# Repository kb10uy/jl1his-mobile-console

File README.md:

# JL1HIS Moblile Console

## License

firmware/app/assets/ 以下のテキスト群はそれぞれのファイルの出典に基づく。
それ以外は各ディレクトリの LICENSE ファイルに準ずる。

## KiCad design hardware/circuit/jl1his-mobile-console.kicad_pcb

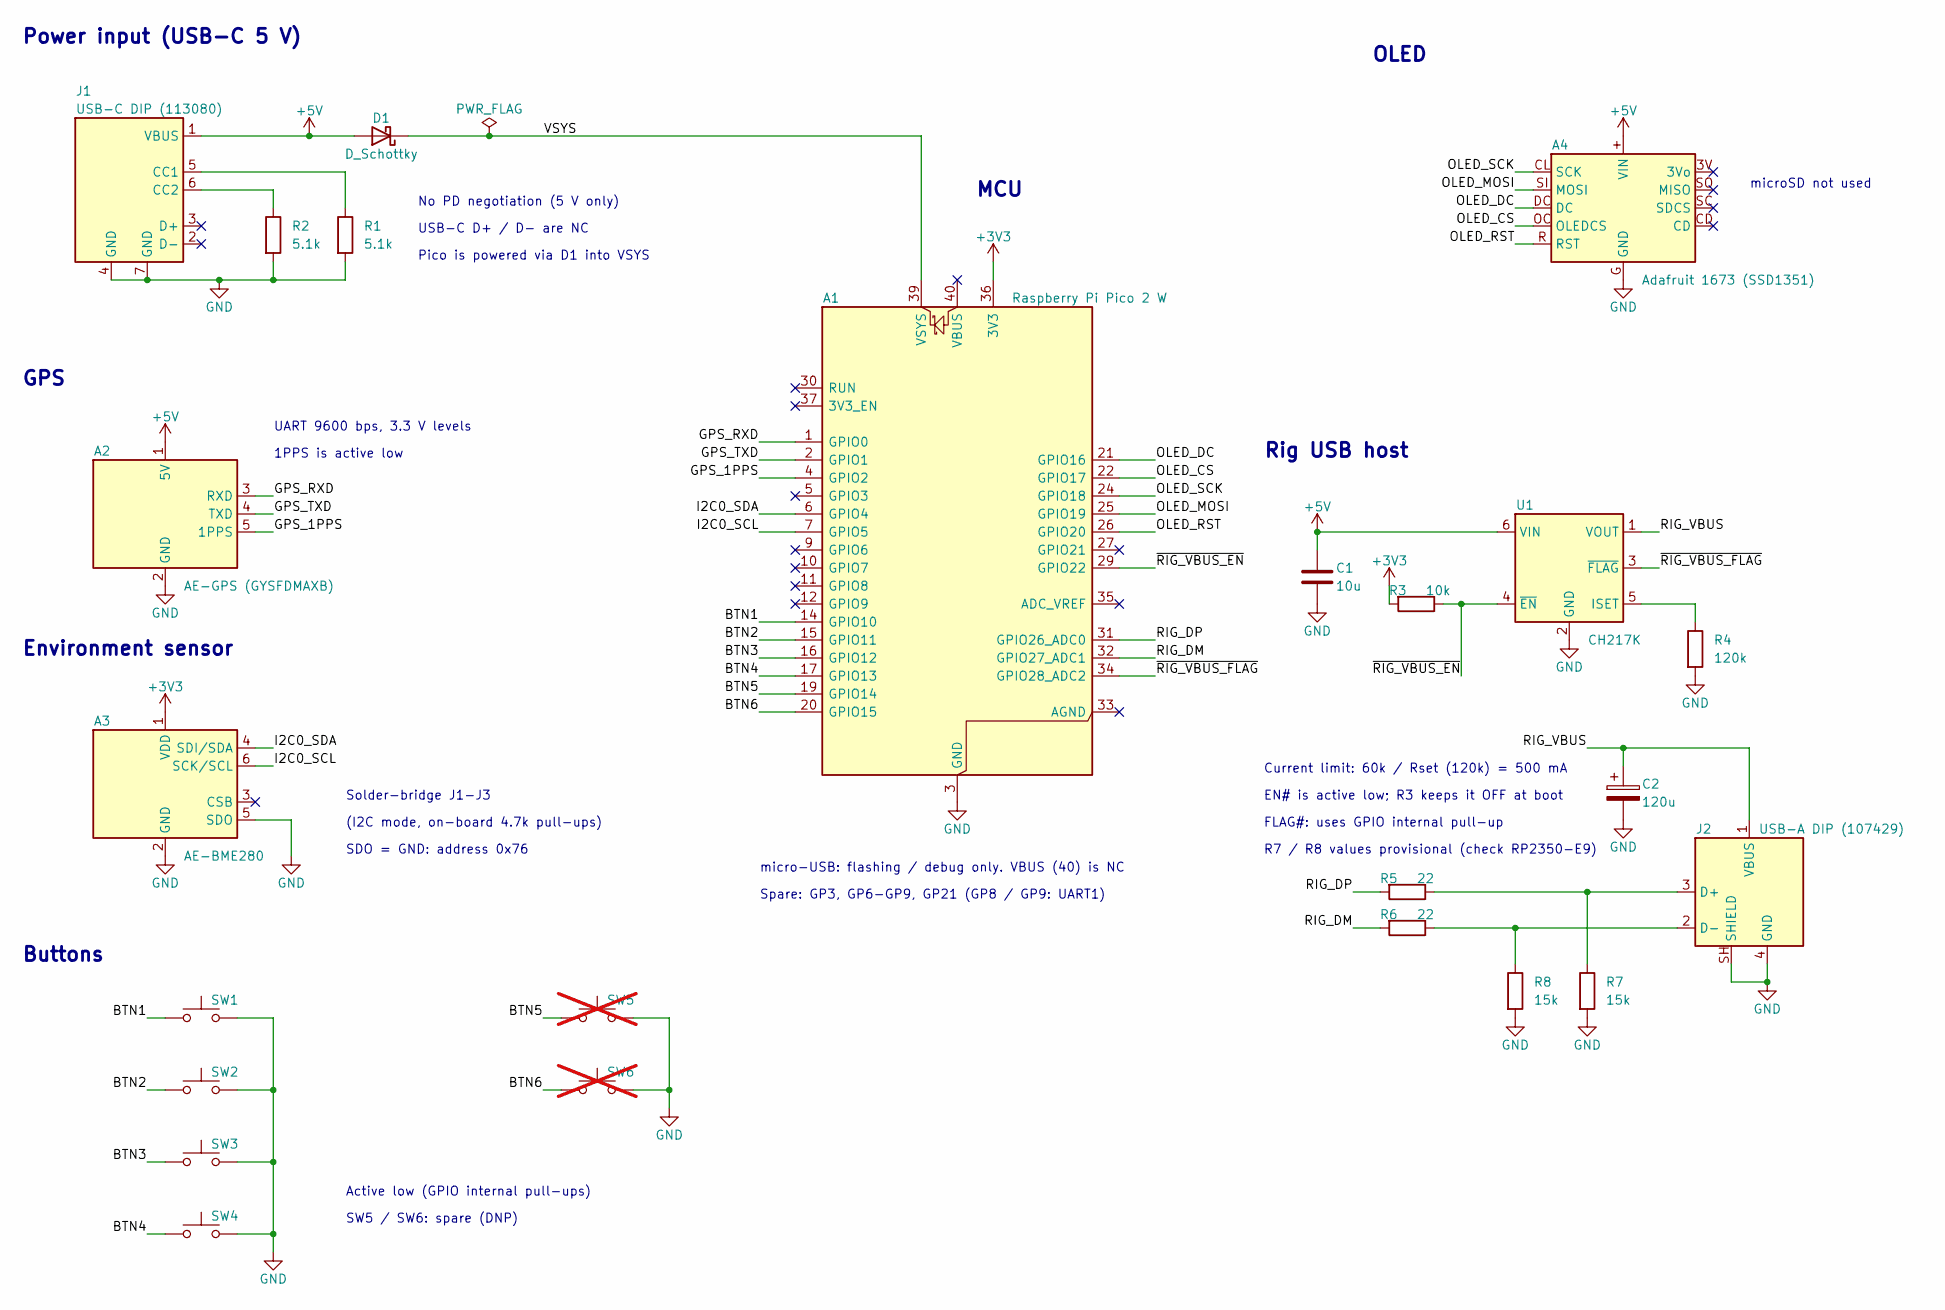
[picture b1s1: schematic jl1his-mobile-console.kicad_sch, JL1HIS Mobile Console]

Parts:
A1: Raspberry Pi Pico 2 W; RaspberryPi_Pico_Common_THT
A2: AE-GPS (GYSFDMAXB); AE-GPS_GYSFDMAXB
A3: AE-BME280
A4: Adafruit 1673 (SSD1351); Adafruit_1673_OLED
C1: 10u; C_Disc_D5.0mm_W2.5mm_P5.00mm
C2: 120u; CP_Radial_D6.3mm_P2.50mm
D1: D_Schottky; D_DO-41_SOD81_P7.62mm_Horizontal
J1: USB-C DIP (113080); Akizuki_AE-USB2.0-TYPE-C
J2: USB-A DIP (107429); Akizuki_AE-USB-A-DIP
R1, R2: 5.1k; R_Axial_DIN0204_L3.6mm_D1.6mm_P7.62mm_Horizontal
R3: 10k; R_Axial_DIN0204_L3.6mm_D1.6mm_P7.62mm_Horizontal
R4: 120k; R_Axial_DIN0204_L3.6mm_D1.6mm_P7.62mm_Horizontal
R5, R6: 22; R_Axial_DIN0204_L3.6mm_D1.6mm_P7.62mm_Horizontal
R7, R8: 15k; R_Axial_DIN0204_L3.6mm_D1.6mm_P7.62mm_Horizontal
SW1, SW2, SW3, SW4: SW_Push; SW_Tactile_6mm_P7.62x5.08
SW5, SW6: SW_Push; SW_Tactile_6mm_P7.62x5.08; not fitted
U1: CH217K; DIP-6_W7.62mm

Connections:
+3V3: A1.36 (3V3), A3.1 (VDD), R3.2
+5V: A2.1 (5V), A4.+ (VIN), C1.1, D1.2 (A), J1.1 (VBUS), U1.6 (VIN)
/BTN1: A1.14 (GPIO10), SW1.1
/BTN2: A1.15 (GPIO11), SW2.1
/BTN3: A1.16 (GPIO12), SW3.1
/BTN4: A1.17 (GPIO13), SW4.1
/BTN5: A1.19 (GPIO14), SW5.1
/BTN6: A1.20 (GPIO15), SW6.1
/GPS_1PPS: A1.4 (GPIO2), A2.5 (1PPS)
/GPS_RXD: A1.1 (GPIO0), A2.3 (RXD)
/GPS_TXD: A1.2 (GPIO1), A2.4 (TXD)
/I2C0_SCL: A1.7 (GPIO5), A3.6 (SCK/SCL)
/I2C0_SDA: A1.6 (GPIO4), A3.4 (SDI/SDA)
/OLED_CS: A1.22 (GPIO17), A4.OC (OLEDCS)
/OLED_DC: A1.21 (GPIO16), A4.DC
/OLED_MOSI: A1.25 (GPIO19), A4.SI (MOSI)
/OLED_RST: A1.26 (GPIO20), A4.R (RST)
/OLED_SCK: A1.24 (GPIO18), A4.CL (SCK)
/RIG_DM: A1.32 (GPIO27_ADC1), R6.2
/RIG_DP: A1.31 (GPIO26_ADC0), R5.2
/RIG_VBUS: C2.1, J2.1 (VBUS), U1.1 (VOUT)
/VSYS: A1.39 (VSYS), D1.1 (K)
/~RIG_VBUS_EN: A1.29 (GPIO22), R3.1, U1.4 (~EN)
/~RIG_VBUS_FLAG: A1.34 (GPIO28_ADC2), U1.3 (~FLAG)
GND: A1.3 (GND), A1.8 (GND), A1.13 (GND), A1.18 (GND), A1.23 (GND), A1.28 (GND), A1.38 (GND), A2.2 (GND), A3.2 (GND), A3.5 (SDO), A4.G (GND), C1.2, C2.2, J1.4 (GND), J1.7 (GND), J2.4 (GND), J2.SH (SHIELD), R1.2, R2.2, R4.2, R7.2, R8.2, SW1.2, SW2.2, SW3.2, SW4.2, SW5.2, SW6.2, U1.2 (GND)
unnamed: J1.5 (CC1), R1.1
unnamed: J1.6 (CC2), R2.1
unnamed: J2.3 (D+), R5.1, R7.1
unnamed: J2.2 (D-), R6.1, R8.1
unnamed: R4.1, U1.5 (ISET)

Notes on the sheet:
SDO = GND: address 0x76
Rig USB host
No PD negotiation (5 V only)
Buttons
OLED
EN# is active low; R3 keeps it OFF at boot
GPS
SW5 / SW6: spare (DNP)
micro-USB: flashing / debug only. VBUS (40) is NC
Environment sensor
Pico is powered via D1 into VSYS
Active low (GPIO internal pull-ups)
microSD not used
Spare: GP3, GP6-GP9, GP21 (GP8 / GP9: UART1)
Current limit: 60k / Rset (120k) = 500 mA
USB-C D+ / D- are NC
R7 / R8 values provisional (check RP2350-E9)
Power input (USB-C 5 V)
(I2C mode, on-board 4.7k pull-ups)
UART 9600 bps, 3.3 V levels
1PPS is active low
MCU
Solder-bridge J1-J3
FLAG#: uses GPIO internal pull-up

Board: 2 copper layers, 25 parts (0 on the bottom side), 30 nets, no tracks yet.

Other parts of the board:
BRD1: AK1E013A 95x72; UniversalBoard_AK1E013A_Portrait
